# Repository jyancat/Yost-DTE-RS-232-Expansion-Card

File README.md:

# Yost DTE RS-232 Expansion Card
 This is the files for RS-232 broken out to Yost DTE standards on a RJ45 connector. Uses the FT231XS-R for UART conversion and the HIN213EIAZ for RS232 conversion. UNTESTED

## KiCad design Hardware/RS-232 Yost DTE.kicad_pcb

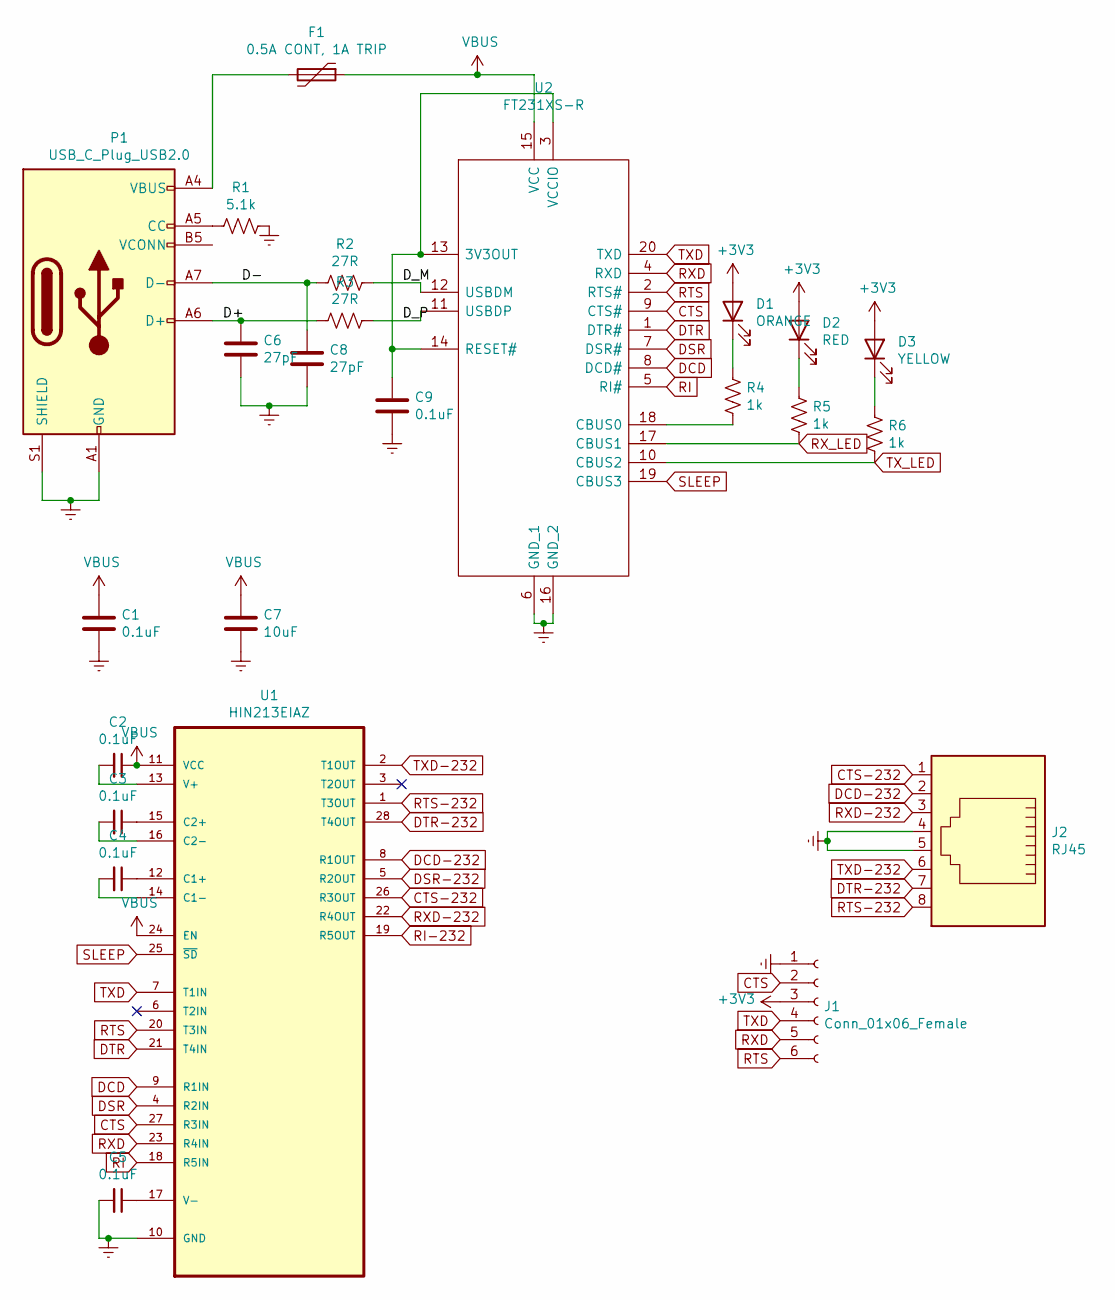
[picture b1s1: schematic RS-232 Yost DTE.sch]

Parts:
C1, C2, C3, C4, C5, C9: 0.1uF; C_0402_1005Metric
C6, C8: 27pF; C_0402_1005Metric
C7: 10uF; C_0402_1005Metric
D1: ORANGE; LED_0603_1608Metric
D2: RED; LED_0603_1608Metric
D3: YELLOW; LED_0603_1608Metric
F1: 0.5A CONT, 1A TRIP; Fuse_0805_2012Metric_Castellated
J1: Conn_01x06_Female; PinHeader_1x06_P2.54mm_Vertical
J2: RJ45; RJ45_Amphenol_RJHSE5380
P1: USB_C_Plug_USB2.0; USB_C_Plug_Molex_105444
R1: 5.1k; R_0402_1005Metric
R2, R3: 27R; R_0402_1005Metric
R4, R5, R6: 1k; R_0603_1608Metric
U1: HIN213EIAZ; SOP65P780X200-28N; MPN HIN213EIAZ
U2: FT231XS-R; SOP64P599X175-20N; Manufacturer_Part_Number FT231XS-R; Mouser Part Number 895-FT231XS-R

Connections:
+3V3: D1.2 (A), D2.2 (A), D3.2 (A), J1.3
/D+: C6.1, P1.A6 (D+), R3.2
/D-: C8.1, P1.A7 (D-), R2.1
/D_M: R2.2, U2.12 (USBDM)
/D_P: R3.1, U2.11 (USBDP)
CTS: J1.2, U1.27 (R3IN), U2.9 (CTS#)
CTS-232: J2.1, U1.26 (R3OUT)
DCD: U1.9 (R1IN), U2.8 (DCD#)
DCD-232: J2.2, U1.8 (R1OUT)
DSR: U1.4 (R2IN), U2.7 (DSR#)
DSR-232: U1.5 (R2OUT)
DTR: U1.21 (T4IN), U2.1 (DTR#)
DTR-232: J2.7, U1.28 (T4OUT)
Earth: C1.2, C5.2, C6.2, C7.2, C8.2, C9.2, J1.1, J2.4, J2.5, P1.A1 (GND), P1.A12 (GND), P1.B1 (GND), P1.B12 (GND), P1.S1 (SHIELD), R1.1, U1.10 (GND), U2.6 (GND_1), U2.16 (GND_2)
unnamed: C2.2, U1.13 (V+)
unnamed: C3.1, U1.15 (C2+)
unnamed: C3.2, U1.16 (C2-)
unnamed: C4.1, U1.12 (C1+)
unnamed: C4.2, U1.14 (C1-)
unnamed: C5.1, U1.17 (V-)
unnamed: C9.1, U2.3 (VCCIO), U2.13 (3V3OUT), U2.14 (RESET#)
unnamed: D1.1 (K), R4.1
unnamed: D2.1 (K), R5.1
unnamed: D3.1 (K), R6.1
unnamed: F1.2, P1.A4 (VBUS), P1.A9 (VBUS), P1.B4 (VBUS), P1.B9 (VBUS)
unnamed: P1.A5 (CC), R1.2
unnamed: R4.2, U2.18 (CBUS0)
RI: U1.18 (R5IN), U2.5 (RI#)
RI-232: U1.19 (R5OUT)
RTS: J1.6, U1.20 (T3IN), U2.2 (RTS#)
RTS-232: J2.8, U1.1 (T3OUT)
RXD: J1.5, U1.23 (R4IN), U2.4 (RXD)
RXD-232: J2.3, U1.22 (R4OUT)
RX_LED: R5.2, U2.17 (CBUS1)
SLEEP: U1.25 (~SD), U2.19 (CBUS3)
TXD: J1.4, U1.7 (T1IN), U2.20 (TXD)
TXD-232: J2.6, U1.2 (T1OUT)
TX_LED: R6.2, U2.10 (CBUS2)
VBUS: C1.1, C2.1, C7.1, F1.1, U1.11 (VCC), U1.24 (EN), U2.15 (VCC)

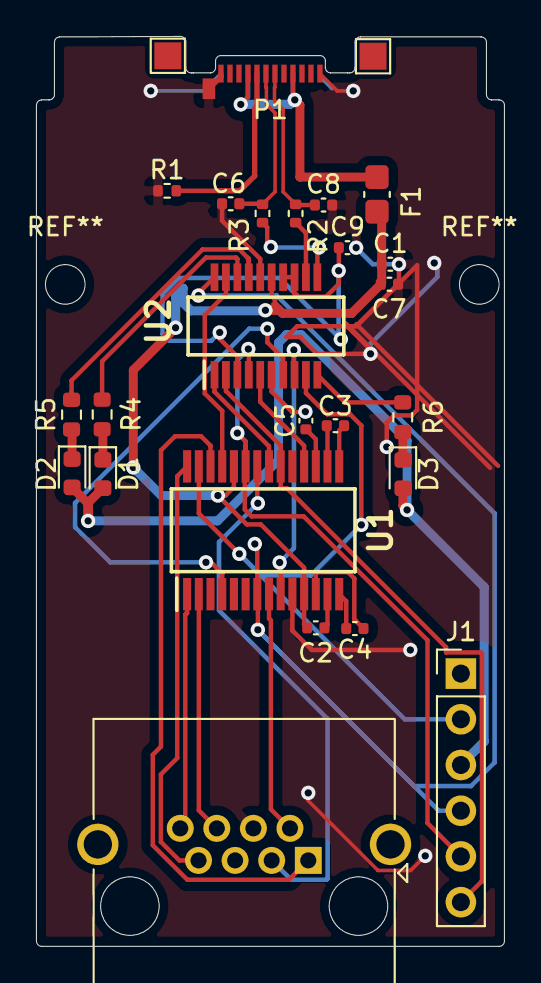
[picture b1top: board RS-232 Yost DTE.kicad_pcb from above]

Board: 2 copper layers, 26.0 x 50.6 mm, 26 parts (0 on the bottom side), 37 nets.

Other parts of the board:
TP1, TP3: TestPoint; TestPoint_Pad_1.5x1.5mm

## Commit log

2022-05-10 Stuff
2022-05-10 Updated SMT Assembly files
2022-05-11 Updated files
    Centering
2022-05-11 Updates
    remember to check orientations
2022-05-28 Updated files
